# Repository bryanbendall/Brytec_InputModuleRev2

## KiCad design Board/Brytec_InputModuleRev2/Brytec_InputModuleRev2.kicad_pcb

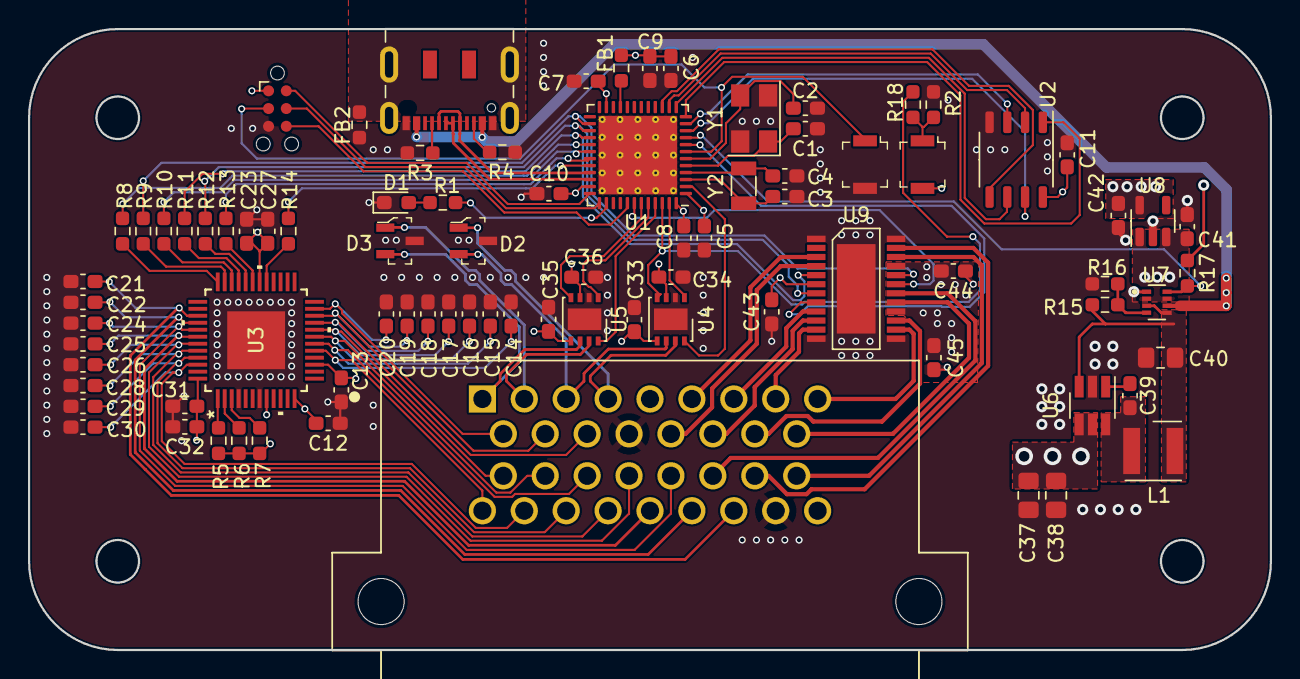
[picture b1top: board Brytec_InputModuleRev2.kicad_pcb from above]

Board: 4 copper layers, 88.9 x 44.5 mm, 85 parts (0 on the bottom side), 88 nets.

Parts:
C1, C2, C3, C4: 10pF; C_0603_1608Metric_Pad1.08x0.95mm_HandSolder
C5, C7, C8, C10, C11, C12, C13, C27, C32, C33, C34, C35, C36, C39, C43, C44, C45: 0.1uF; C_0603_1608Metric_Pad1.08x0.95mm_HandSolder
C6, C23, C31, C41, C42: 1uF; C_0603_1608Metric_Pad1.08x0.95mm_HandSolder
C9: 10nF; C_0603_1608Metric_Pad1.08x0.95mm_HandSolder
C14, C15, C16, C17, C18, C19, C20, C21, C22, C24, C25, C26, C28, C29, C30: 6.8nF; C_0603_1608Metric_Pad1.08x0.95mm_HandSolder
C37: 4.7uF; C_0805_2012Metric_Pad1.18x1.45mm_HandSolder
C38: 0.1uF; C_0805_2012Metric_Pad1.18x1.45mm_HandSolder
C40: 10uF; C_0805_2012Metric_Pad1.18x1.45mm_HandSolder
D1: LED_Small; LED_0603_1608Metric_Pad1.05x0.95mm_HandSolder
D2, D3: PESD2CAN_215; SOT-23-3
FB1, FB2: FerriteBead_Small; R_0603_1608Metric_Pad0.98x0.95mm_HandSolder
J1: Conn_ARM_SWD_TagConnect_TC2030-NL; Tag-Connect_TC2030-IDC-NL_2x03_P1.27mm_Vertical
J2: USB_C_Receptacle_USB2.0; USB_C_Receptacle_JAE_DX07S016JA1R1500
J3: 6437288-2; TE_6437288-2
L1: 6.8uH; L_Wurth_WE-LQSH-4020
R1: 65; R_0603_1608Metric_Pad0.98x0.95mm_HandSolder
R2, R15, R16, R17: 10K; R_0603_1608Metric_Pad0.98x0.95mm_HandSolder
R3, R4: 5.1K; R_0603_1608Metric_Pad0.98x0.95mm_HandSolder
R5: 50K; R_0603_1608Metric_Pad0.98x0.95mm_HandSolder
R6: 9K; R_0603_1608Metric_Pad0.98x0.95mm_HandSolder
R7: 180; R_0603_1608Metric_Pad0.98x0.95mm_HandSolder
R8, R9, R10, R11, R12, R13, R14: 1K; R_0603_1608Metric_Pad0.98x0.95mm_HandSolder
R18: 0; R_0603_1608Metric_Pad0.98x0.95mm_HandSolder
S1, S2: B3U-1000P; Switch_Tactile_SMD_B3U-1000P
U1: STM32G491CEUx; QFN-48-1EP_7x7mm_P0.5mm_EP5.6x5.6mm_ThermalVias
U2: MB85RS64; SSOP-8_3.9x5.05mm_P1.27mm
U3: L9966CB-TR; TQFP48_L9966_STM
U4, U5: MCP2558FD-xMF; DFN-8-1EP_3x3mm_P0.65mm_EP1.55x2.4mm
U6: LMR50410Y5FQDBVRQ1; SOT-23-6_Handsoldering
U7: TPS2116DRLR; SOTFL50P160X60-8N
U8: AP2112K-3.3; SOT-23-5
U9: TLE94112ES; Infineon_TSDSO-24
Y1: 8MHz; Crystal_SMD_5032-4Pin_5.0x3.2mm
Y2: 32.768kHz; Crystal_SMD_3215-2Pin_3.2x1.5mm

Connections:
+3.3V: C5.2, C6.2, C7.2, C8.2, C9.2, C10.2, C11.1, C33.1, C35.1, C42.1, C43.2, FB1.1, J1.1 (VCC), R17.1, S2.2, U1.1 (VBAT), U1.23 (VDD), U1.35 (VDD), U1.48 (VDD), U2.8 (VDD), U4.5 (VIO), U5.5 (VIO), U8.5 (VOUT), U9.6 (VDD)
+5V: C12.2, C23.1, C27.1, C34.1, C36.1, C41.1, J3.5, R5.1, R6.1, R7.1, U3.8 (VDD5REF), U3.12 (VI5V), U3.30 (VDD5V), U4.3 (VDD), U5.3 (VDD), U7.2 (VOUT), U7.7 (VOUT), U8.1 (VIN), U8.3 (EN)
/Mcu/Memory_Hold: U1.10 (PA2), U2.7 (~HOLD)
/Mcu/Memory_Wp: U1.11 (PA3), U2.3 (~WP)
/Mcu/RESET: J1.3 (~RESET), S1.1, U1.7 (PG10)
/Mcu/SWCLK: J1.4 (SWCLK), U1.37 (PA14)
/Mcu/SWDIO: J1.2 (SWDIO), U1.36 (PA13)
/Mcu/SWO: J1.6 (SWO), U1.41 (PB3)
/Mcu/Usb D+: J2.A6 (D+), J2.B6 (D+), U1.34 (PA12)
/Mcu/Usb D-: J2.A7 (D-), J2.B7 (D-), U1.33 (PA11)
/Mcu/Usb_Shield: FB2.1, J2.S1 (SHIELD)
/Mcu/User_Led: R1.1, U1.38 (PA15)
Can1+: D2.1 (C1), J3.4, U4.7 (CANH)
Can1-: D2.2 (C2), J3.3, U4.6 (CANL)
Can1Rx: R18.1, U1.46 (PB8), U4.4 (RXD)
Can1Silent: U1.2 (PC13), U4.8 (S)
Can1Tx: U1.47 (PB9), U4.1 (TXD)
Can2+: D3.1 (C1), J3.2, U5.7 (CANH)
Can2-: D3.2 (C2), J3.1, U5.6 (CANL)
Can2Rx: U1.43 (PB5), U5.4 (RXD)
Can2Silent: U1.45 (PB7), U5.8 (S)
Can2Tx: U1.44 (PB6), U5.1 (TXD)
GND: C1.1, C2.1, C3.1, C4.1, C5.1, C6.1, C7.1, C8.1, C9.1, C10.1, C11.2, C12.1, C13.1, C14.2, C15.2, C16.2, C17.2, C18.2, C19.2, C20.2, C21.2, C22.2, C23.2, C24.2, C25.2, C26.2, C27.2, C28.2, C29.2, C30.2, C31.2, C32.2, C33.2, C34.2, C35.2, C36.2, C37.2, C38.2, C40.2, C41.2, C42.2, C43.1, C44.1, C45.1, D1.1 (K), D2.3 (C3), D3.3 (C3), FB2.2, J1.5 (GND), J2.A1 (GND), J2.A12 (GND), J2.B1 (GND), J2.B12 (GND), J3.13, J3.33, R2.2, R3.2, R4.2, R16.2, S1.2, U1.49 (VSS), U2.4 (GND), U3.4 (R_GND), U3.7 (GND), U3.EPAD, U4.2 (VSS), U4.9 (VSS), U5.2 (VSS), U5.9 (VSS), U6.2 (GND), U7.1 (GND), U8.2 (GND), U9.1 (GND), U9.12 (GND), U9.13 (GND), U9.24 (GND), U9.EDP (GND), Y1.2, Y1.4
Ignition: C13.2, C31.1, C32.1, C37.1, C38.1, C44.2, C45.2, J3.34, U3.15 (VIX), U3.48 (UBSW), U6.4 (EN), U6.5 (VIN), U9.16 (VS1), U9.21 (VS2)
Input1: C30.1, J3.27, U3.46 (IO_5)
Input2: C29.1, J3.28, U3.45 (IO_6)
Input3: C28.1, J3.29, U3.44 (IO_7)
Input4: C26.1, J3.21, U3.43 (IO_8)
Input5: C25.1, J3.30, U3.42 (IO_9)
Input6: C24.1, J3.22, U3.41 (IO_10)
Input7: C22.1, J3.31, U3.40 (IO_11)
Input8: C21.1, J3.32, U3.39 (IO_12)
Input9: C14.1, J3.26, U3.17 (IO_13)
Input10: C15.1, J3.20, U3.18 (IO_14)
Input11: C16.1, J3.19, U3.19 (IO_15)
Input12: C17.1, J3.18, U3.20 (IO_1)
Input13: C18.1, J3.12, U3.21 (IO_2)
Input14: C19.1, J3.11, U3.22 (IO_3)
Input15: C20.1, J3.10, U3.23 (IO_4)
L6699-Int: R14.2, U1.32 (PA10)
L6699-Rst: R8.2, U1.29 (PC6)
L6699-Sync: R13.2, U1.31 (PA9)
unnamed: D1.2 (A), R1.2
unnamed: J2.A5 (CC1), R4.1
unnamed: J2.B5 (CC2), R3.1
unnamed: R2.1, R18.2, S2.1
unnamed: C3.2, U1.3 (PC14), Y2.2
unnamed: C4.2, U1.4 (PC15), Y2.1
unnamed: C1.2, U1.5 (PF0), Y1.1
unnamed: C2.2, U1.6 (PF1), Y1.3
unnamed: FB1.2, U1.21 (VDDA)
unnamed: R10.1, U3.34 (CS)
unnamed: R14.1, U3.29 (INT)
unnamed: R12.1, U3.32 (MISO)
unnamed: R11.1, U3.33 (MOSI)
unnamed: R7.2, U3.3 (RR1)
unnamed: R6.2, U3.2 (RR2)
unnamed: R5.2, U3.1 (RR3)
unnamed: R8.1, U3.36 (RST)
unnamed: R9.1, U3.35 (SCLK)
unnamed: R13.1, U3.31 (SYNC)
unnamed: C39.2, U6.1 (CB)
unnamed: C39.1, L1.1, U6.6 (SW)
unnamed: R15.2, R16.1, U7.4 (PR1)
Out2: J3.24, U9.23 (OUT2)
Out3: J3.9, U9.14 (OUT3)
Out4: J3.8, U9.11 (OUT4)
Out5: J3.6, U9.3 (OUT5)
Out6: J3.15, U9.10 (OUT6)
Out7: J3.14, U9.4 (OUT7)
Out8: J3.25, U9.22 (OUT8)
Out9: J3.7, U9.9 (OUT9)
Out10: J3.16, U9.15 (OUT10)
Out11: J3.17, U9.17 (OUT11)
Out12: J3.23, U9.18 (OUT12)
PowerSwitchStatus: R17.2, U1.9 (PA1), U7.8 (ST)
Regulated 5V: C40.1, L1.2, R15.1, U6.3 (FB), U7.3 (VIN1), U7.5 (MODE)
SPI1_Miso: U1.14 (PA6), U2.2 (SO)
SPI1_Mosi: U1.15 (PA7), U2.5 (SI)
SPI1_SS: U1.12 (PA4), U2.1 (~CS)
SPI1_Sclk: U1.13 (PA5), U2.6 (SCK)
SPI2_Miso: R12.2, U1.27 (PB14), U9.7 (SDO)
SPI2_Mosi: R11.2, U1.28 (PB15), U9.5 (SDI)
SPI2_SS_L9966: R10.2, U1.30 (PA8)
SPI2_SS_TLE94112: U1.42 (PB4), U9.19 (CSN)
SPI2_Sclk: R9.2, U1.26 (PB13), U9.20 (SCLK)
TLE94112_EN: U1.8 (PA0), U9.8 (EN)
Usb 5V: J2.A4 (VBUS), J2.A9 (VBUS), J2.B4 (VBUS), J2.B9 (VBUS), U7.6 (VIN2)

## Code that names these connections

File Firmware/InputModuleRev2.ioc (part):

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Mcu.Name=STM32G491C(C-E)Ux
Mcu.Package=UFQFPN48
Mcu.UserName=STM32G491CEUx
PA0.GPIOParameters=GPIO_Label
PA0.GPIO_Label=TLE94112_EN
PA0.Signal=GPIO_Output
PA1.GPIOParameters=GPIO_Label
PA1.GPIO_Label=PowerSwitchStatus
PA1.Signal=GPIO_Input
PA10.GPIOParameters=GPIO_Label
PA10.GPIO_Label=L9966-Int
PA10.Signal=GPIO_Input
PA11.Mode=Device
PA11.Signal=USB_DM
PA12.Mode=Device
PA12.Signal=USB_DP
PA13.Mode=Serial_Wire
PA13.Signal=SYS_JTMS-SWDIO
PA14.Mode=Serial_Wire
PA14.Signal=SYS_JTCK-SWCLK
PA15.GPIOParameters=GPIO_Label
PA15.GPIO_Label=User_Led
PA15.Signal=GPIO_Output
PA2.GPIOParameters=PinState,GPIO_Label
PA2.GPIO_Label=Memory_Hold
PA2.PinState=GPIO_PIN_SET
PA2.Signal=GPIO_Output
PA3.GPIOParameters=PinState,GPIO_Label
PA3.GPIO_Label=Memory_Wp
PA3.PinState=GPIO_PIN_SET
PA3.Signal=GPIO_Output
PA4.GPIOParameters=PinState,GPIO_Label
PA4.GPIO_Label=Memory_SS
PA4.PinState=GPIO_PIN_SET
PA4.Signal=GPIO_Output
PA5.Mode=Full_Duplex_Master
PA5.Signal=SPI1_SCK
PA6.Mode=Full_Duplex_Master
PA6.Signal=SPI1_MISO
PA7.Mode=Full_Duplex_Master
PA7.Signal=SPI1_MOSI
PA8.GPIOParameters=PinState,GPIO_Label
PA8.GPIO_Label=SPI_SS_L9966
PA8.PinState=GPIO_PIN_SET
PA8.Signal=GPIO_Output
PA9.GPIOParameters=GPIO_Label
PA9.GPIO_Label=L9966-Sync
PA9.Signal=GPIO_Output
PB13.Mode=Full_Duplex_Master
PB13.Signal=SPI2_SCK
PB14.Mode=Full_Duplex_Master
PB14.Signal=SPI2_MISO
PB15.Mode=Full_Duplex_Master
PB15.Signal=SPI2_MOSI
PB4.GPIOParameters=PinState,GPIO_Label
PB4.GPIO_Label=SPI2_SS_TLE94112
PB4.PinState=GPIO_PIN_SET
PB4.Signal=GPIO_Output
PB5.Mode=FDCAN_Activate
PB5.Signal=FDCAN2_RX
PB6.Mode=FDCAN_Activate
PB6.Signal=FDCAN2_TX
PB7.GPIOParameters=GPIO_Label
PB7.GPIO_Label=Can2Silent
PB7.Signal=GPIO_Output
PB8-BOOT0.Mode=FDCAN_Activate
PB8-BOOT0.Signal=FDCAN1_RX
PB9.Mode=FDCAN_Activate
PB9.Signal=FDCAN1_TX
PC13.GPIOParameters=GPIO_Label
PC13.GPIO_Label=Can1Silent
PC13.Signal=GPIO_Output
PC14-OSC32_IN.Mode=LSE-External-Oscillator
PC14-OSC32_IN.Signal=RCC_OSC32_IN
PC15-OSC32_OUT.Mode=LSE-External-Oscillator
PC15-OSC32_OUT.Signal=RCC_OSC32_OUT
PC6.GPIOParameters=GPIO_Label
PC6.GPIO_Label=L9966-Rst
PC6.Signal=GPIO_Output
PF0-OSC_IN.Mode=HSE-External-Oscillator
PF0-OSC_IN.Signal=RCC_OSC_IN
PF1-OSC_OUT.Mode=HSE-External-Oscillator
PF1-OSC_OUT.Signal=RCC_OSC_OUT
RCC.HSE_VALUE=8000000
RCC.SYSCLKFreq_VALUE=144000000
RCC.SYSCLKSource=RCC_SYSCLKSOURCE_PLLCLK
board=custom

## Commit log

2023-08-29 Added git ignore
2023-08-29 Initial Board Work
2023-09-02 Added microcontroller config
2023-09-02 Updated board
2024-01-26 Board Files
2024-01-26 Initial generated files
2024-01-26 Removed submodule problem
2024-01-27 Initial project setup
2024-01-27 Change can bus defs into cpp file
2024-01-30 Updated for spi changes
2024-02-01 Updating board file
2024-02-03 Setup spi in config Set pin defaults
2024-02-18 Init us delay Working board with led
2024-02-19 Overwrite config for dual can bus
2024-03-02 Working tle94112
2024-03-03 Working board Changing Spi for different chips
2024-05-09 Updates for submodules
2024-07-19 Added 5v mod
2024-07-19 Added jump to bootloader
2025-04-26 Set all outputs of TLE94112 after update
